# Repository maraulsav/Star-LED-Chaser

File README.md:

# Star-LED-Chaser
Hi! I am Maritza and in this project I made a 555 LED Chaser with a PCB that look like a star.
I wanted to make it as a keychain

## 3D  View
Front

Back

## Features
- NE555P (555 TImer)
- CD4017 (Integrated Circuit)
- 10 LEDs
- 2 Capacitor
- 2 Resistor
- 1 Variable Resistor
- 1 Slide witch
- 1 Battery Socket

## PCB
My PCB is made in KiCad
These are the footprints I used
- Battery: BatteryHolder_Keystone_3000_1x12mm
- Capacitor_THT:CP_Radial D5.0mm_P2.00mm
- LED_THT:LED_D3.0mm
- Resistor_THT:R_Axial_DIN0207_L6.3mm_D2.5mm_P7.62mm_Horizontal
- SW SPST: Button Switch THT:SW DIP SPSTx01 Slide 9.78x4.72mm W7.62mm P2.54mm
- TestPoint: Connector PinSocket 2.54mm:PinSocket 1x01 P2.54mm Vertical
- NE555P: Package_DIP: DIP-8_W7.62mm
- 4017: footprints: N16

Schematic

PCB

## BOM
Here should be everything that u need to make this keychain
- 1x NE555P (555 TImer)
- 1x CD4017 (Integrated Circuit)
- 10x LEDs
- 2x Capacitor
- 2x Resistor
- 1x Variable Resistor
- 1x Slide witch
- 1x Battery Socket

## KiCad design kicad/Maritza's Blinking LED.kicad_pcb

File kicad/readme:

Hello This folder contain all my kicad files
Including .pro .sch and .pcb

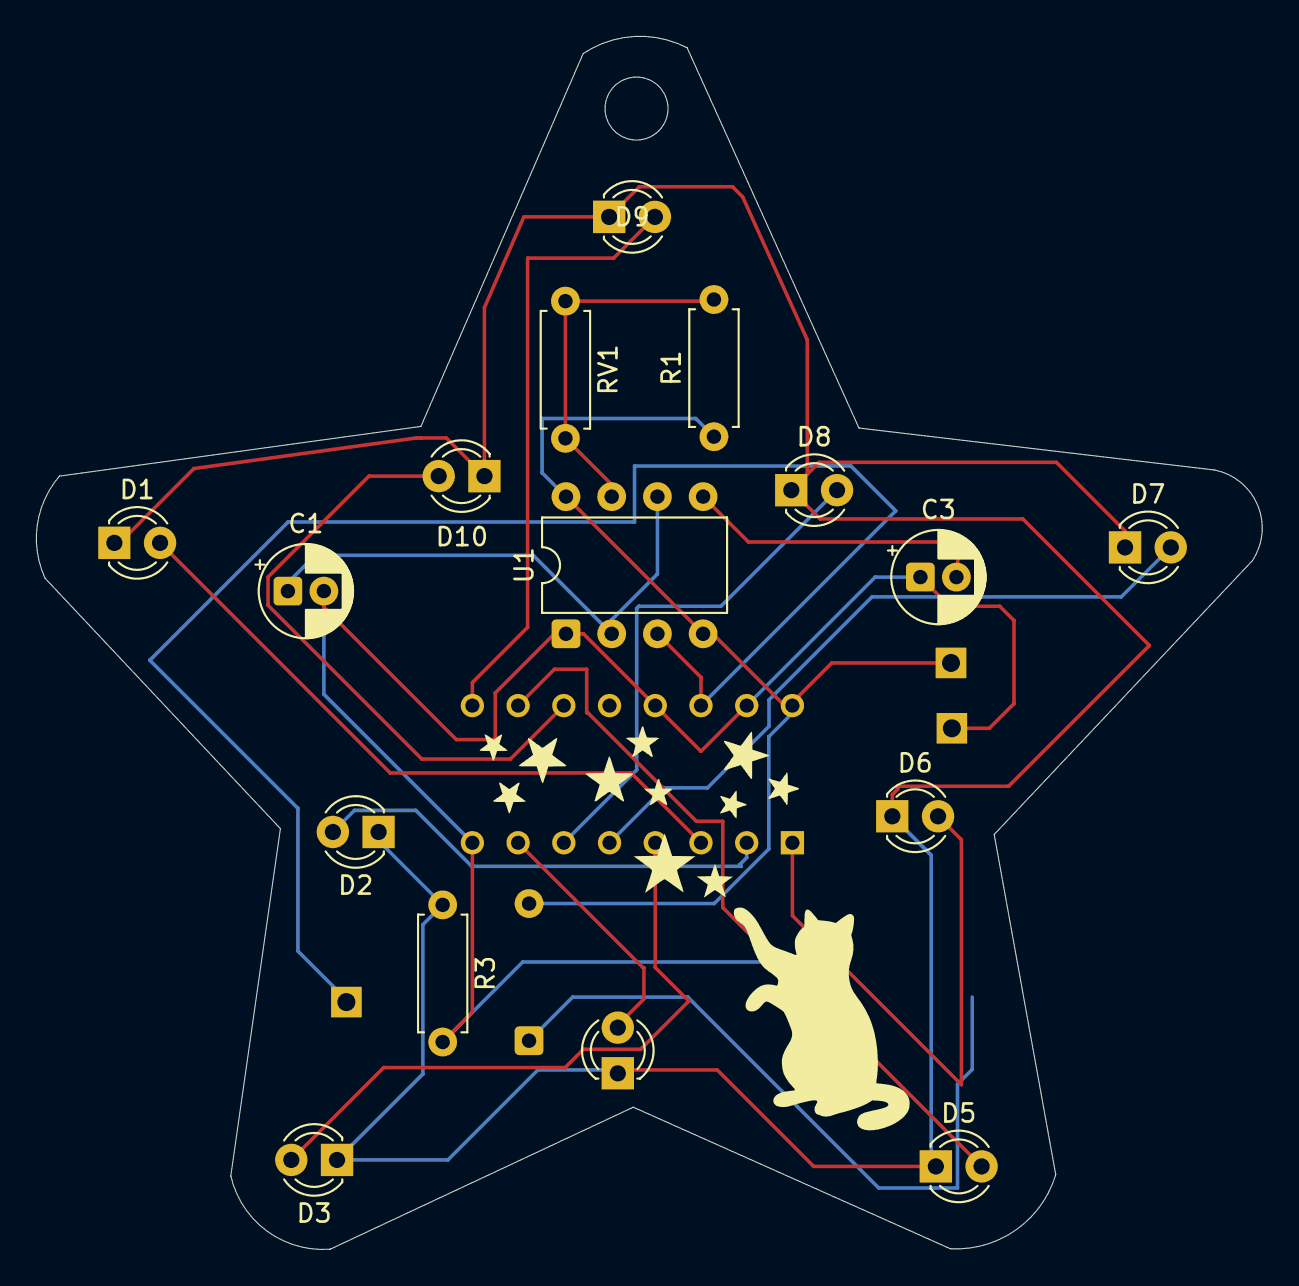
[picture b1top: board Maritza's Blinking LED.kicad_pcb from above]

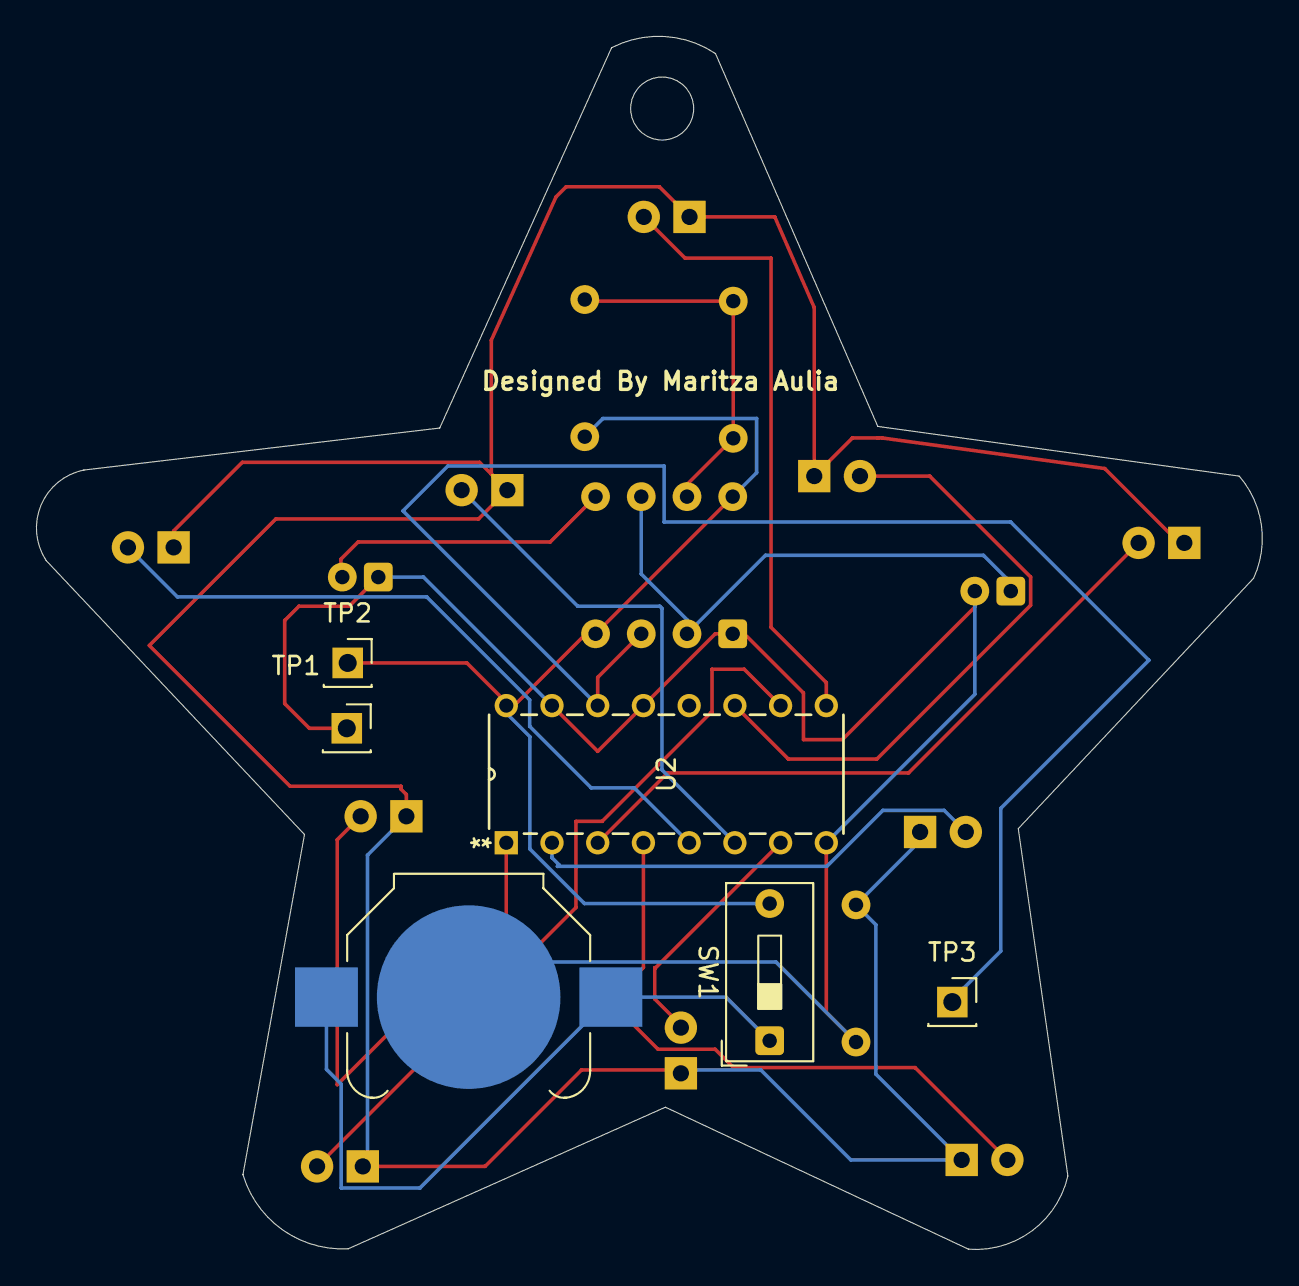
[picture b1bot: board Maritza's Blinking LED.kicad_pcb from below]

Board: 2 copper layers, 68.1 x 67.4 mm, 23 parts (6 on the bottom side), 18 nets.

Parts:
BT2: Battery_Cell; BatteryHolder_Keystone_3000_1x12mm
C1: 1 uF; CP_Radial_D5.0mm_P2.00mm
C3: 0.01 uF; CP_Radial_D5.0mm_P2.00mm
Cat: LOGO; CatAndStarFF
D1, D2, D3, D4, D5, D6, D7, D8, D9, D10: LED; LED_D3.0mm
R1: 1k; R_Axial_DIN0207_L6.3mm_D2.5mm_P7.62mm_Horizontal
R3: 470; R_Axial_DIN0207_L6.3mm_D2.5mm_P7.62mm_Horizontal
RV1: 50k; R_Axial_DIN0207_L6.3mm_D2.5mm_P7.62mm_Horizontal
SW1: SW_SPST; SW_DIP_SPSTx01_Slide_9.78x4.72mm_W7.62mm_P2.54mm
TP1, TP2, TP3: TestPoint; PinSocket_1x01_P2.54mm_Vertical
U1: NE555P; DIP-8_W7.62mm
U2: 4017; N16

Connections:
+5V: R1.1, SW1.2 (B), TP2.1, U1.4 (R), U1.8 (VCC), U2.16 (VDD)
GND: BT2.2 (-), C1.2, C3.1, R3.2, TP1.1, U1.1 (GND), U2.8 (VSS), U2.13 (CKEN), U2.15 (Reset)
unnamed: BT2.1 (+), SW1.1 (A)
unnamed: D1.2 (A), U2.3 (Q0)
unnamed: D1.1 (K), D2.1 (K), D3.1 (K), D4.1 (K), D5.1 (K), D6.1 (K), D7.1 (K), D8.1 (K), D9.1 (K), D10.1 (K), R3.1
unnamed: D2.2 (A), U2.2 (Q1)
unnamed: D3.2 (A), U2.4 (Q2)
unnamed: D4.2 (A), U2.7 (Q3)
unnamed: D5.2 (A), U2.10 (Q4)
unnamed: D6.2 (A), U2.1 (Q5)
unnamed: D7.2 (A), U2.5 (Q6)
unnamed: D8.2 (A), U2.6 (Q7)
unnamed: D9.2 (A), U2.9 (Q8)
unnamed: D10.2 (A), U2.11 (Q9)
unnamed: C3.2, U1.5 (CV)
unnamed: R1.2, RV1.1, RV1.2, U1.7 (DIS)
OUT: TP3.1, U1.3 (Q), U2.14 (CLK)
TR: C1.1, U1.2 (TR), U1.6 (THR)
